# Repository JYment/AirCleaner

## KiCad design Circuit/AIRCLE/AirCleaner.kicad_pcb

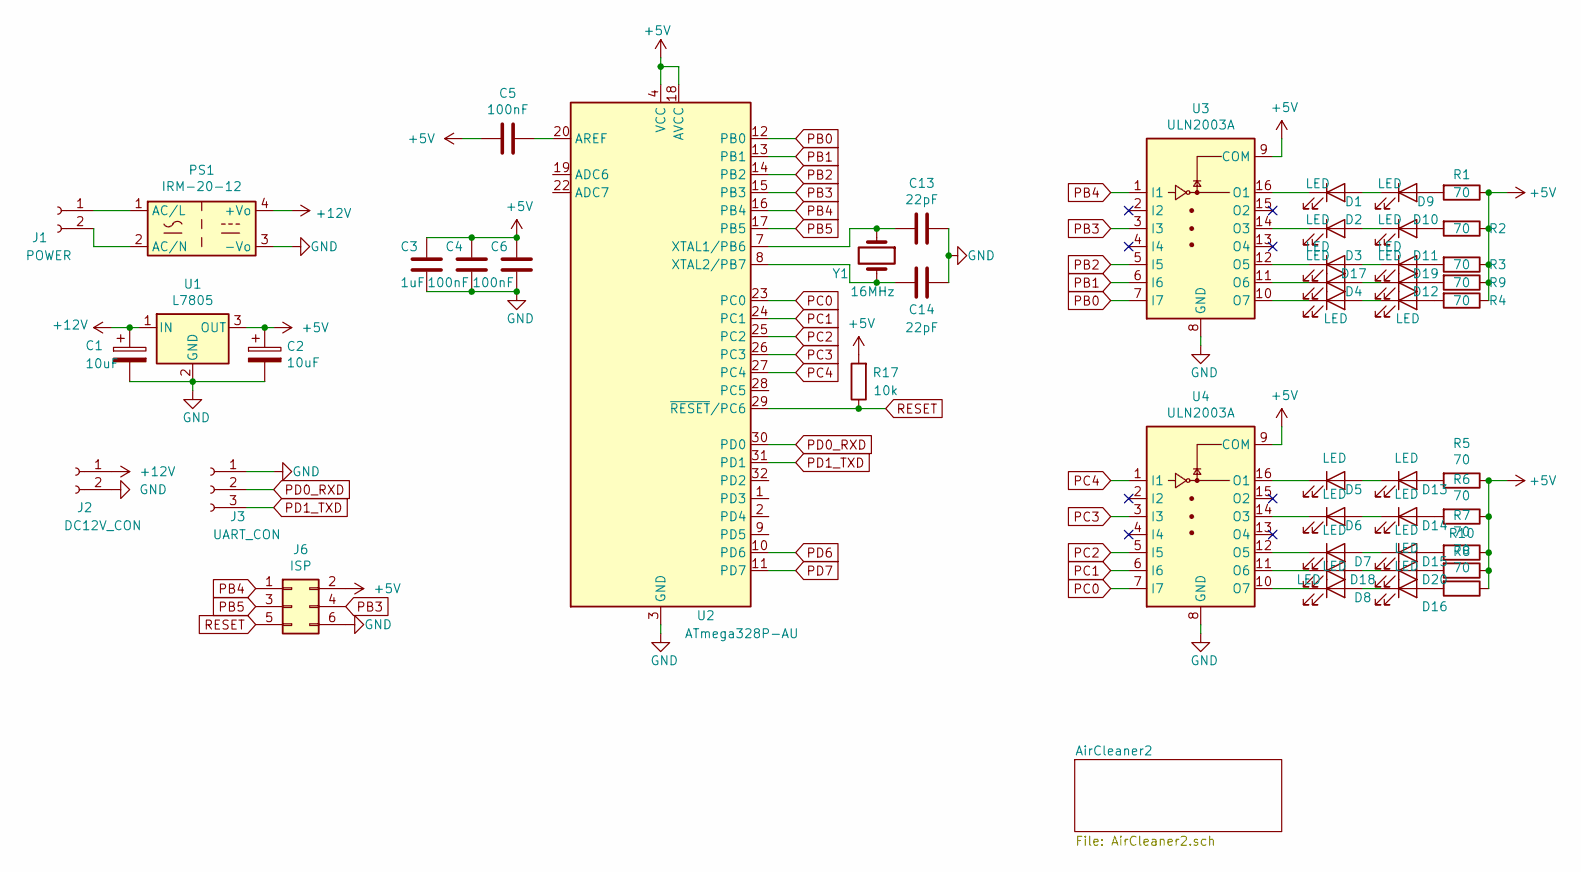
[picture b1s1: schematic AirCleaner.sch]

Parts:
C1, C2: 10uF; C_1206_3216Metric_Pad1.42x1.75mm_HandSolder
C3: 1uF; C_0603_1608Metric_Pad1.05x0.95mm_HandSolder
C4, C5, C6: 100nF; C_0603_1608Metric_Pad1.05x0.95mm_HandSolder
C13, C14: 22pF; C_0603_1608Metric_Pad1.05x0.95mm_HandSolder
D1, D2, D3, D4, D5, D6, D7, D8, D9, D10, D11, D12, D13, D14, D15, D16, D17, D18, D19, D20: LED; LED_0603_1608Metric_Pad1.05x0.95mm_HandSolder
J1: POWER; Connector_BR-950C_2P
J2: DC12V_CON; Molex_SPOX_5267-02A_1x02_P2.50mm_Vertical
J3: UART_CON; Molex_SPOX_5267-03A_1x03_P2.50mm_Vertical
J6: ISP; PinHeader_2x03_P2.54mm_Vertical
PS1: IRM-20-12; Converter_ACDC_MeanWell_IRM-20-xx_THT
R1, R2, R3, R4, R5, R6, R7, R8, R9, R10: 70; R_0603_1608Metric_Pad1.05x0.95mm_HandSolder
R17: 10k; R_0603_1608Metric_Pad1.05x0.95mm_HandSolder
U1: L7805; DPAK
U2: ATmega328P-AU; TQFP-32_7x7mm_P0.8mm
U3, U4: ULN2003A; SOIC-16_3.9x9.9mm_P1.27mm
Y1: 16MHz; Crystal_SMD_HC49-SD

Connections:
+5V: C2.1, C3.2, C4.2, C5.2, C6.2, J6.2, R1.1, R2.1, R3.1, R4.1, R5.1, R6.1, R7.1, R8.1, R9.1, R10.1, R17.2, U1.3 (OUT), U2.4 (VCC), U2.6 (VCC), U2.18 (AVCC), U3.9 (COM), U4.9 (COM)
+12V: C1.1, J2.1, PS1.4 (+Vo), U1.1 (IN)
GND: C1.2, C2.2, C3.1, C4.1, C6.1, C13.1, C14.1, J2.2, J3.1, J6.6, PS1.3 (-Vo), U1.2 (GND), U2.3 (GND), U2.5 (GND), U2.21 (GND), U3.8 (GND), U4.8 (GND)
unnamed: C5.1, U2.20 (AREF)
unnamed: C13.2, U2.7 (XTAL1/PB6), Y1.1
unnamed: C14.2, U2.8 (XTAL2/PB7), Y1.2
unnamed: D1.1 (K), U3.16 (O1)
unnamed: D1.2 (A), D9.1 (K)
unnamed: D2.1 (K), U3.14 (O3)
unnamed: D3.1 (K), U3.12 (O5)
unnamed: D4.1 (K), U3.10 (O7)
unnamed: D5.1 (K), U4.16 (O1)
unnamed: D6.1 (K), U4.14 (O3)
unnamed: D7.1 (K), U4.12 (O5)
unnamed: D8.1 (K), U4.10 (O7)
unnamed: D9.2 (A), R1.2
unnamed: D2.2 (A), D10.1 (K)
unnamed: D10.2 (A), R2.2
unnamed: D3.2 (A), D11.1 (K)
unnamed: D11.2 (A), R3.2
unnamed: D4.2 (A), D12.1 (K)
unnamed: D12.2 (A), R4.2
unnamed: D5.2 (A), D13.1 (K)
unnamed: D13.2 (A), R5.2
unnamed: D6.2 (A), D14.1 (K)
unnamed: D14.2 (A), R6.2
unnamed: D7.2 (A), D15.1 (K)
unnamed: D15.2 (A), R7.2
unnamed: D8.2 (A), D16.1 (K)
unnamed: D16.2 (A), R8.2
unnamed: D17.1 (K), U3.11 (O6)
unnamed: D17.2 (A), D19.1 (K)
unnamed: D18.1 (K), U4.11 (O6)
unnamed: D18.2 (A), D20.1 (K)
unnamed: D19.2 (A), R9.2
unnamed: D20.2 (A), R10.2
unnamed: J1.1, PS1.1 (AC/L)
unnamed: J1.2, PS1.2 (AC/N)
PB0: U2.12 (PB0), U3.7 (I7)
PB1: U2.13 (PB1), U3.6 (I6)
PB2: U2.14 (PB2), U3.5 (I5)
PB3: J6.4, U2.15 (PB3), U3.3 (I3)
PB4: J6.1, U2.16 (PB4), U3.1 (I1)
PB5: J6.3, U2.17 (PB5)
PC0: U2.23 (PC0), U4.7 (I7)
PC1: U2.24 (PC1), U4.6 (I6)
PC2: U2.25 (PC2), U4.5 (I5)
PC3: U2.26 (PC3), U4.3 (I3)
PC4: U2.27 (PC4), U4.1 (I1)
PD0_RXD: J3.2, U2.30 (PD0)
PD1_TXD: J3.3, U2.31 (PD1)
PD6: U2.10 (PD6)
PD7: U2.11 (PD7)
RESET: J6.5, R17.1, U2.29 (~RESET~/PC6)

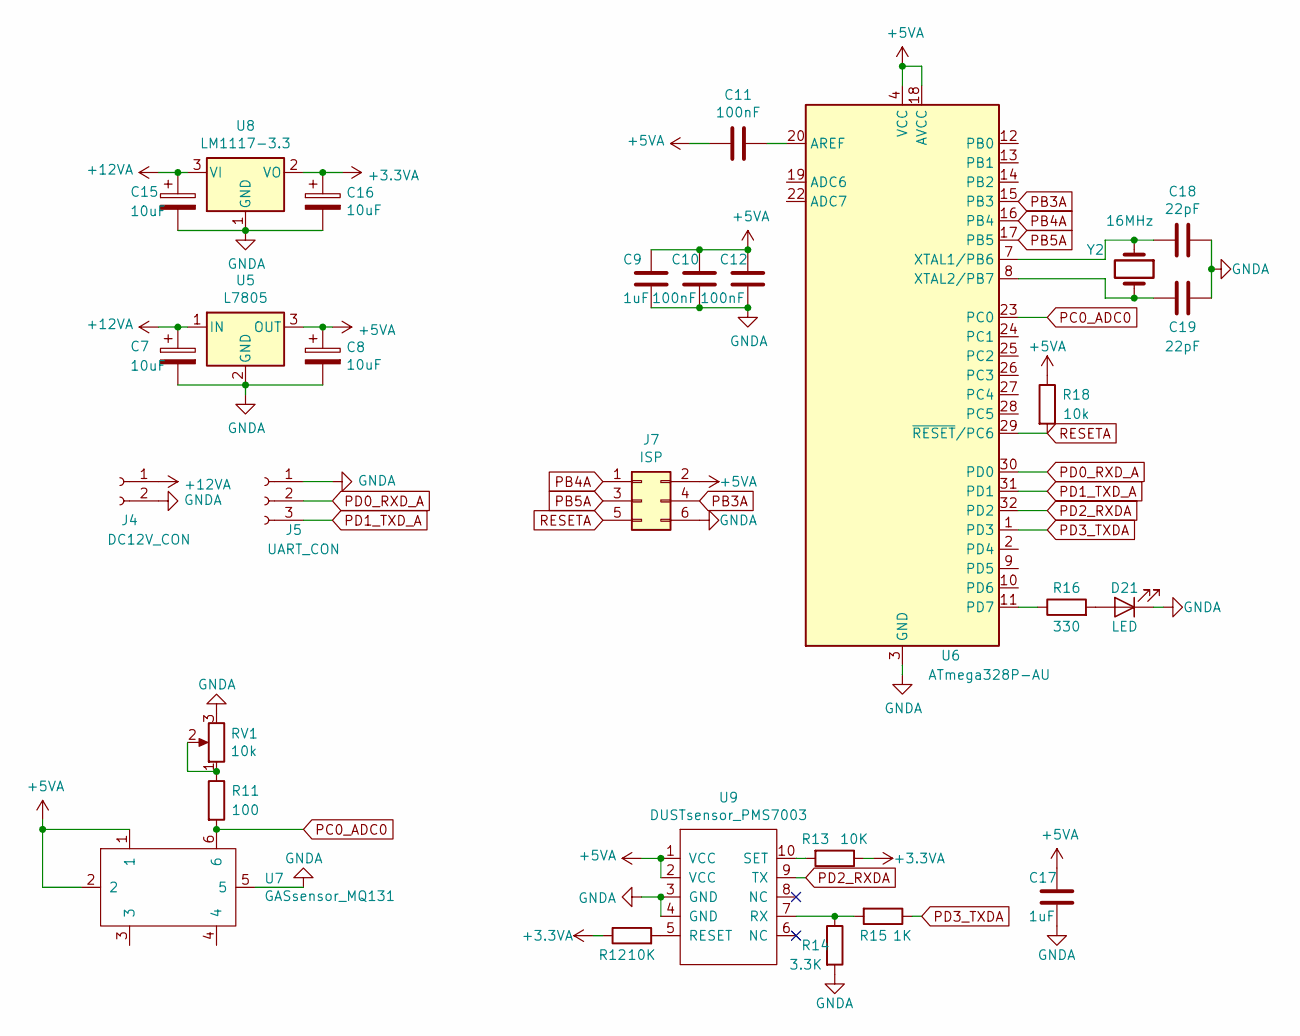
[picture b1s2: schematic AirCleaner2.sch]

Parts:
C7, C8, C15, C16: 10uF; C_1206_3216Metric_Pad1.42x1.75mm_HandSolder
C9, C17: 1uF; C_0603_1608Metric_Pad1.05x0.95mm_HandSolder
C10, C11, C12: 100nF; C_0603_1608Metric_Pad1.05x0.95mm_HandSolder
C18, C19: 22pF; C_0603_1608Metric_Pad1.05x0.95mm_HandSolder
D21: LED; LED_0603_1608Metric_Pad1.05x0.95mm_HandSolder
J4: DC12V_CON; Molex_SPOX_5267-02A_1x02_P2.50mm_Vertical
J5: UART_CON; Molex_SPOX_5267-03A_1x03_P2.50mm_Vertical
J7: ISP; PinHeader_2x03_P2.54mm_Vertical
R11: 100; R_0603_1608Metric_Pad1.05x0.95mm_HandSolder
R12, R13: 10K; R_0603_1608Metric_Pad1.05x0.95mm_HandSolder
R14: 3.3K; R_0603_1608Metric_Pad1.05x0.95mm_HandSolder
R15: 1K; R_0603_1608Metric_Pad1.05x0.95mm_HandSolder
R16: 330; R_0603_1608Metric_Pad1.05x0.95mm_HandSolder
R18: 10k; R_0603_1608Metric_Pad1.05x0.95mm_HandSolder
RV1: 10k; Potentiometer_Bourns_3296W_Vertical
U5: L7805; DPAK
U6: ATmega328P-AU; TQFP-32_7x7mm_P0.8mm
U7: GASsensor_MQ131
U8: LM1117-3.3; SOT-223-3_TabPin2
U9: DUSTsensor_PMS7003
Y2: 16MHz; Crystal_SMD_HC49-SD

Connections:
+3.3VA: C16.1, R12.1, R13.1, U8.2 (VO)
+5VA: C8.1, C9.2, C10.2, C11.2, C12.2, C17.2, J7.2, R18.1, U5.3 (OUT), U6.4 (VCC), U6.6 (VCC), U6.18 (AVCC), U7.1, U7.2, U9.1 (VCC), U9.2 (VCC)
+12VA: C7.1, C15.1, J4.1, U5.1 (IN), U8.3 (VI)
GNDA: C7.2, C8.2, C9.1, C10.1, C12.1, C15.2, C16.2, C17.1, C18.1, C19.1, D21.1 (K), J4.2, J5.1, J7.6, R14.2, RV1.3, U5.2 (GND), U6.3 (GND), U6.5 (GND), U6.21 (GND), U7.5, U8.1 (GND), U9.3 (GND), U9.4 (GND)
unnamed: C11.1, U6.20 (AREF)
unnamed: C18.2, U6.7 (XTAL1/PB6), Y2.1
unnamed: C19.2, U6.8 (XTAL2/PB7), Y2.2
unnamed: D21.2 (A), R16.2
unnamed: R11.1, RV1.1, RV1.2
unnamed: R12.2, U9.5 (RESET)
unnamed: R13.2, U9.10 (SET)
unnamed: R14.1, R15.2, U9.7 (RX)
unnamed: R16.1, U6.11 (PD7)
PB3A: J7.4, U6.15 (PB3)
PB4A: J7.1, U6.16 (PB4)
PB5A: J7.3, U6.17 (PB5)
PC0_ADC0: R11.2, U6.23 (PC0), U7.6
PD0_RXD_A: J5.2, U6.30 (PD0)
PD1_TXD_A: J5.3, U6.31 (PD1)
PD2_RXDA: U6.32 (PD2), U9.9 (TX)
PD3_TXDA: R15.1, U6.1 (PD3)
RESETA: J7.5, R18.2, U6.29 (~RESET~/PC6)

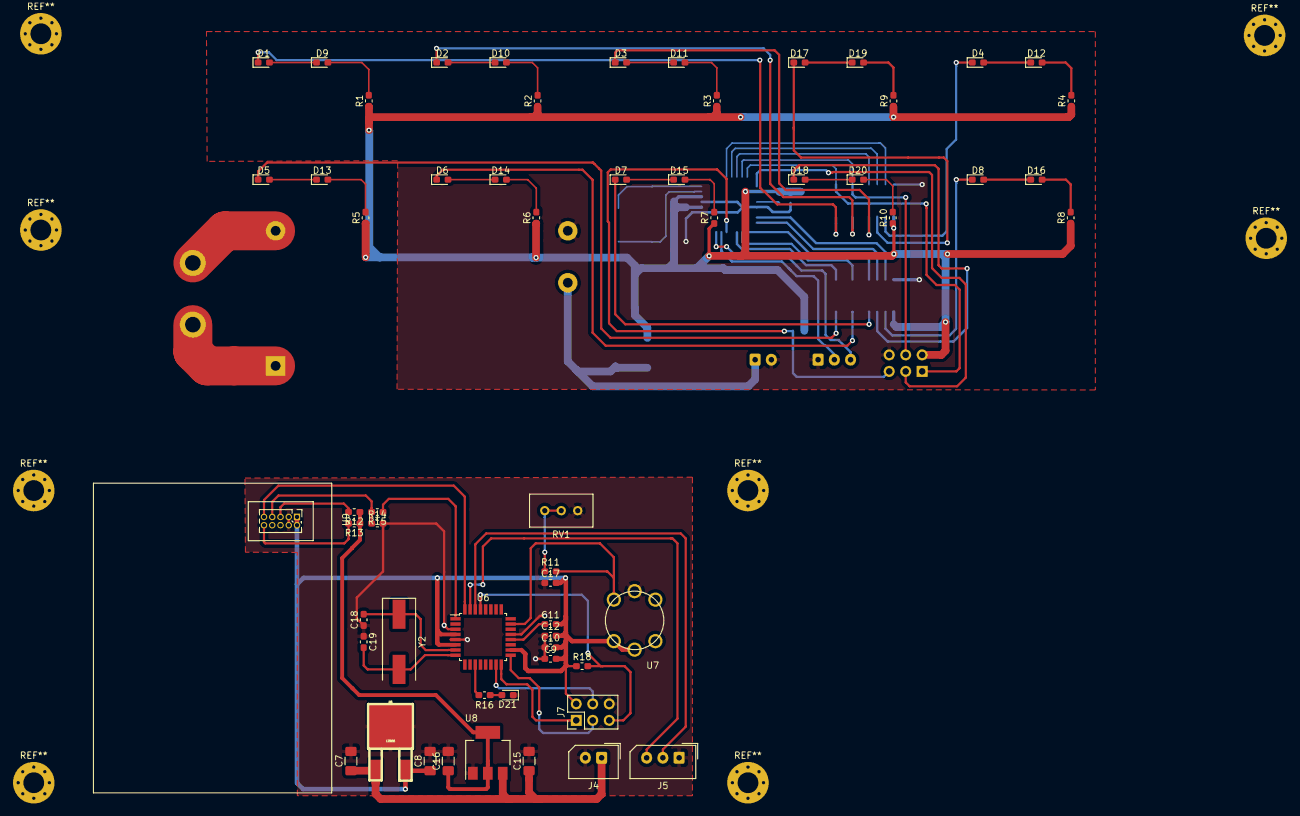
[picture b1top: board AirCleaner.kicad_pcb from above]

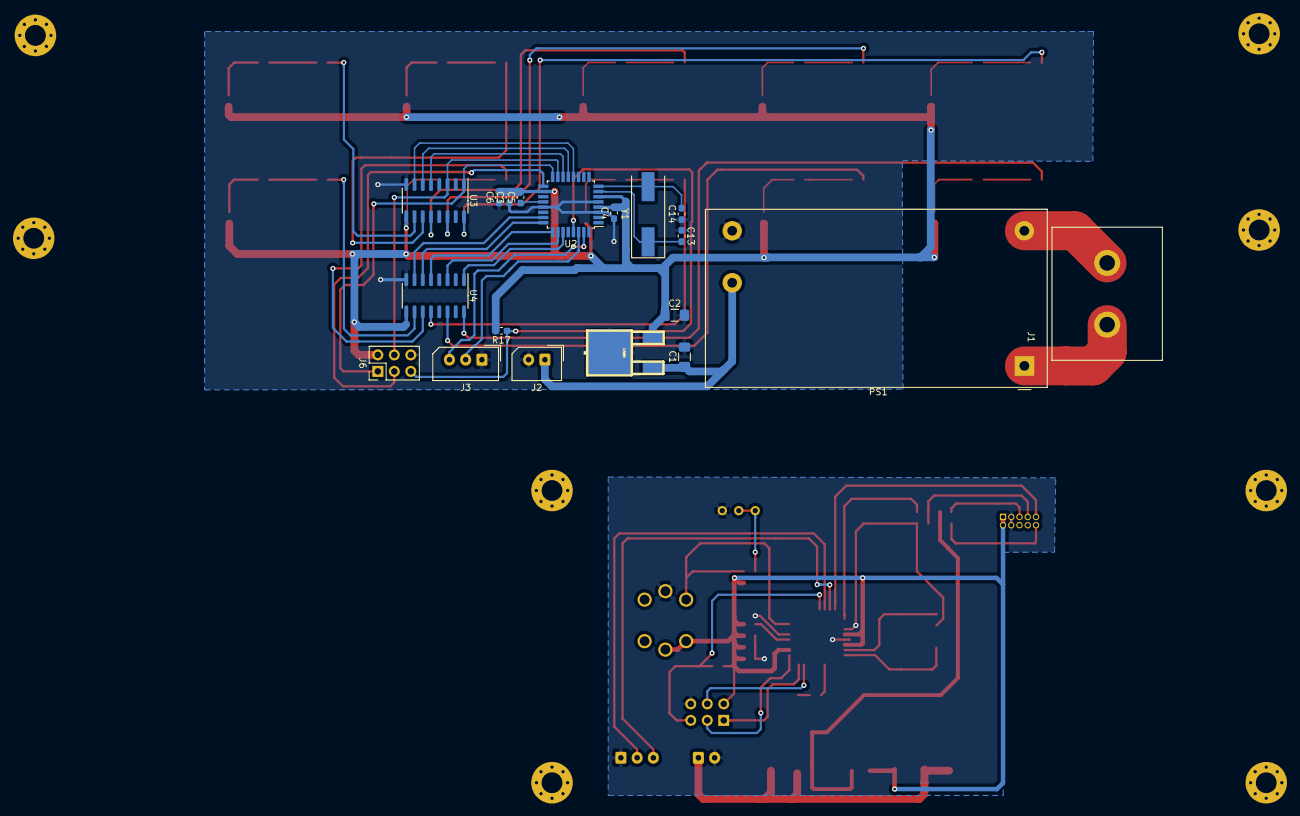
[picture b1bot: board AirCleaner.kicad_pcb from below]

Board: 2 copper layers, 78 parts (19 on the bottom side), 74 nets.

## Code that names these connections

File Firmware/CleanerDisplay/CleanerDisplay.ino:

#include <MsTimer2.h>

#define STX     0xC8
#define ETX     0x5A
#define GAS_LEVEL_1     0x1A
#define GAS_LEVEL_2     0x2B
#define GAS_LEVEL_3     0x3C
#define GAS_LEVEL_4     0x4D
#define GAS_LEVEL_5     0x5E
#define DUST_LEVEL_1    0x1A
#define DUST_LEVEL_2     0x2B
#define DUST_LEVEL_3     0x3C
#define DUST_LEVEL_4     0x4D
#define DUST_LEVEL_5     0x5E

unsigned char data[5];
unsigned char data_dust;
unsigned char data_gas;
char disp_dust_led[5] = {12, 11, 10, 9, 8};
char disp_gas_led[5] = {A4, A3, A2, A1, A0};


void setup() {
    pinMode(8, OUTPUT);             // DUST 4 = PB0
    pinMode(9, OUTPUT);             // DUST 3 = PB1
    pinMode(10, OUTPUT);            // DUST 2 = PB2
    pinMode(11, OUTPUT);            // DUST 1 = PB3
    pinMode(12, OUTPUT);            // DUST 0 = PB4
    pinMode(A0, OUTPUT);            // GAS 4 = PC0
    pinMode(A1, OUTPUT);            // GAS 3 = PC1
    pinMode(A2, OUTPUT);            // GAS 2 = PC2
    pinMode(A3, OUTPUT);            // GAS 1 = PC3
    pinMode(A4, OUTPUT);            // GAS 0 = PC4

    Serial.begin(9600);
    MsTimer2::set(100, get_data);
    MsTimer2::start();
}

void loop() {
    
}

void get_data() {
    char success = data_parsing();
    if(success == 1) {
        data_gas = data[1];
        data_dust = data[2];
        Serial.print(data_gas, HEX);
        Serial.print(data_dust, HEX);
    }
//    Serial.print(">> gas value = ");
//    Serial.println(data_gas);
//    Serial.print(">> Dust value = ");
//    Serial.println(data_dust);

    if(data_gas == GAS_LEVEL_1) {
        digitalWrite(disp_gas_led[0], HIGH);
        digitalWrite(disp_gas_led[1], LOW);
        digitalWrite(disp_gas_led[2], LOW);
        digitalWrite(disp_gas_led[3], LOW);
        digitalWrite(disp_gas_led[4], LOW);
    }
    else if(data_gas == GAS_LEVEL_2) {
        digitalWrite(disp_gas_led[0], HIGH);
        digitalWrite(disp_gas_led[1], HIGH);
        digitalWrite(disp_gas_led[2], LOW);
        digitalWrite(disp_gas_led[3], LOW);
        digitalWrite(disp_gas_led[4], LOW);
    }
    else if(data_gas == GAS_LEVEL_3) {
        digitalWrite(disp_gas_led[0], HIGH);
        digitalWrite(disp_gas_led[1], HIGH);
        digitalWrite(disp_gas_led[2], HIGH);
        digitalWrite(disp_gas_led[3], LOW);
        digitalWrite(disp_gas_led[4], LOW);
    }
    else if(data_gas == GAS_LEVEL_4) {
        digitalWrite(disp_gas_led[0], HIGH);
        digitalWrite(disp_gas_led[1], HIGH);
        digitalWrite(disp_gas_led[2], HIGH);
        digitalWrite(disp_gas_led[3], HIGH);
        digitalWrite(disp_gas_led[4], LOW);
    }
    else if(data_gas == GAS_LEVEL_5) {
        digitalWrite(disp_gas_led[0], HIGH);
        digitalWrite(disp_gas_led[1], HIGH);
        digitalWrite(disp_gas_led[2], HIGH);
        digitalWrite(disp_gas_led[3], HIGH);
        digitalWrite(disp_gas_led[4], HIGH);
    }

    if(data_dust == DUST_LEVEL_1) {
        digitalWrite(disp_dust_led[0], HIGH);
        digitalWrite(disp_dust_led[1], LOW);
        digitalWrite(disp_dust_led[2], LOW);
        digitalWrite(disp_dust_led[3], LOW);
        digitalWrite(disp_dust_led[4], LOW);
    }
    else if(data_dust == DUST_LEVEL_2) {
        digitalWrite(disp_dust_led[0], HIGH);
        digitalWrite(disp_dust_led[1], HIGH);
        digitalWrite(disp_dust_led[2], LOW);
        digitalWrite(disp_dust_led[3], LOW);
        digitalWrite(disp_dust_led[4], LOW);
    }
    else if(data_dust == DUST_LEVEL_3) {
        digitalWrite(disp_dust_led[0], HIGH);
        digitalWrite(disp_dust_led[1], HIGH);
        digitalWrite(disp_dust_led[2], HIGH);
        digitalWrite(disp_dust_led[3], LOW);
        digitalWrite(disp_dust_led[4], LOW);
    }
    else if(data_dust == DUST_LEVEL_4) {
        digitalWrite(disp_dust_led[0], HIGH);
        digitalWrite(disp_dust_led[1], HIGH);
        digitalWrite(disp_dust_led[2], HIGH);
        digitalWrite(disp_dust_led[3], HIGH);
        digitalWrite(disp_dust_led[4], LOW);
    }
    else if(data_dust == DUST_LEVEL_5) {
        digitalWrite(disp_dust_led[0], HIGH);
        digitalWrite(disp_dust_led[1], HIGH);
        digitalWrite(disp_dust_led[2], HIGH);
        digitalWrite(disp_dust_led[3], HIGH);
        digitalWrite(disp_dust_led[4], HIGH);
    }
}


char data_parsing() {
    if(Serial.available()) {
        for(int i=0; i<5; i++) {
            data[i] = Serial.read();
        }
    }

    if(data[0] == STX) {
        if(data[3] == ETX) {
            return 1;
        }
        else {
            return 0;
        }
    }
    else {
        return 0;
    }
}

void data_erase() {
    for(int i=0; i<6; i++) {
        data[i] = 0;
    }
}

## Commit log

2019-12-17 Arduino_Finish
